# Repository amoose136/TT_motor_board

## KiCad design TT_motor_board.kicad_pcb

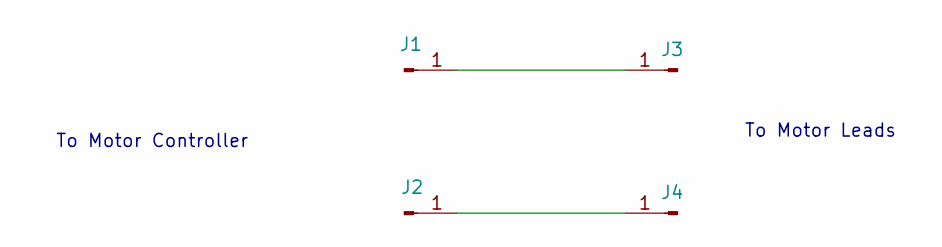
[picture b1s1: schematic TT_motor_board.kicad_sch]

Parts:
J1, J2: Pad; TestPoint_Pad_4.0x4.0mm
J3, J4: CastPad; TestPoint_THTPad_D3.0mm_Drill1.5mm

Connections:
unnamed: J1.1, J3.1
unnamed: J2.1, J4.1

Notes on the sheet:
To Motor Controller
To Motor Leads

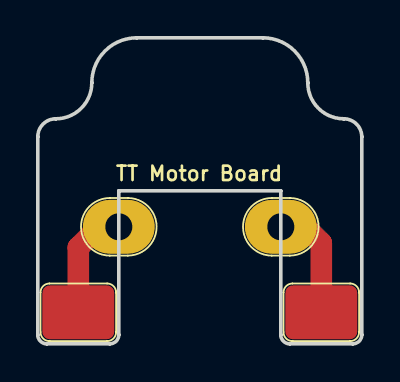
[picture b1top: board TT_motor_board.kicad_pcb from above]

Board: 2 copper layers, 18.0 x 17.0 mm, 4 parts (0 on the bottom side), 2 nets.

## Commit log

2024-06-05 add v0
